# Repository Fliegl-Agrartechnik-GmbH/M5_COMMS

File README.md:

# M5_COMMS
M5_COMMS are CAN-Bus and Modbus Boards for M5 Stack

<https://github.com/espressif/esp-idf/issues/13989>

<https://community.m5stack.com/topic/306/plc-module/12?_=1718738548748>

4 Models: 
(right klick, open in new Tab for high-res view)

1. MAX3485, is a Fully 3.3V RS-485 Transceiver

2. LTC2877IMSE, is a 5V RS-485 Transceiver with a VIO Pin, so can interface to a 3.3V and even 1.8 V MCU

3. MAX485 is a 5V only Transceiver, using the Schottky Diode to not damage the ESP32 at RX.

4. CAN-Bus with a Infineon Transceiver

see: <https://github.com/Fliegl-Agrartechnik-GmbH/M5_COMMS/tree/main/CAN-BUS>

# lic
<p xmlns:cc="http://creativecommons.org/ns#" xmlns:dct="http://purl.org/dc/terms/"><a property="dct:title" rel="cc:attributionURL" href="https://github.com/Fliegl-Agrartechnik-GmbH/M5_COMMS">M5_COMMS</a> by <a rel="cc:attributionURL dct:creator" property="cc:attributionName" href="https://github.com/Fliegl-Agrartechnik-GmbH">Fliegl Agrartechnik GmbH</a> is licensed under <a href="https://creativecommons.org/licenses/by-sa/4.0/?ref=chooser-v1" target="_blank" rel="license noopener noreferrer" style="display:inline-block;">CC BY-SA 4.0</a></p>

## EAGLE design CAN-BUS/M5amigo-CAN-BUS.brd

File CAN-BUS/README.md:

# CAN-BUS

reffered also as TWAI

## Pinout

| **CAN**      | **RX** | **TX** |
|--------------|--------|--------|
| Core (Basic) | G36    | G25    |
| Core 2       | G36    | G25    |
| CoreS3       | G8     | G5     |

## External

| **Pin**  | **1**    | **2** | **3** | **4** |
|----------|----------|-------|-------|-------|
| Function | DC 9-24V | CAN_L | CAN_H | GND   |

## Testing

https://github.com/Fliegl-Agrartechnik-GmbH/twai_network

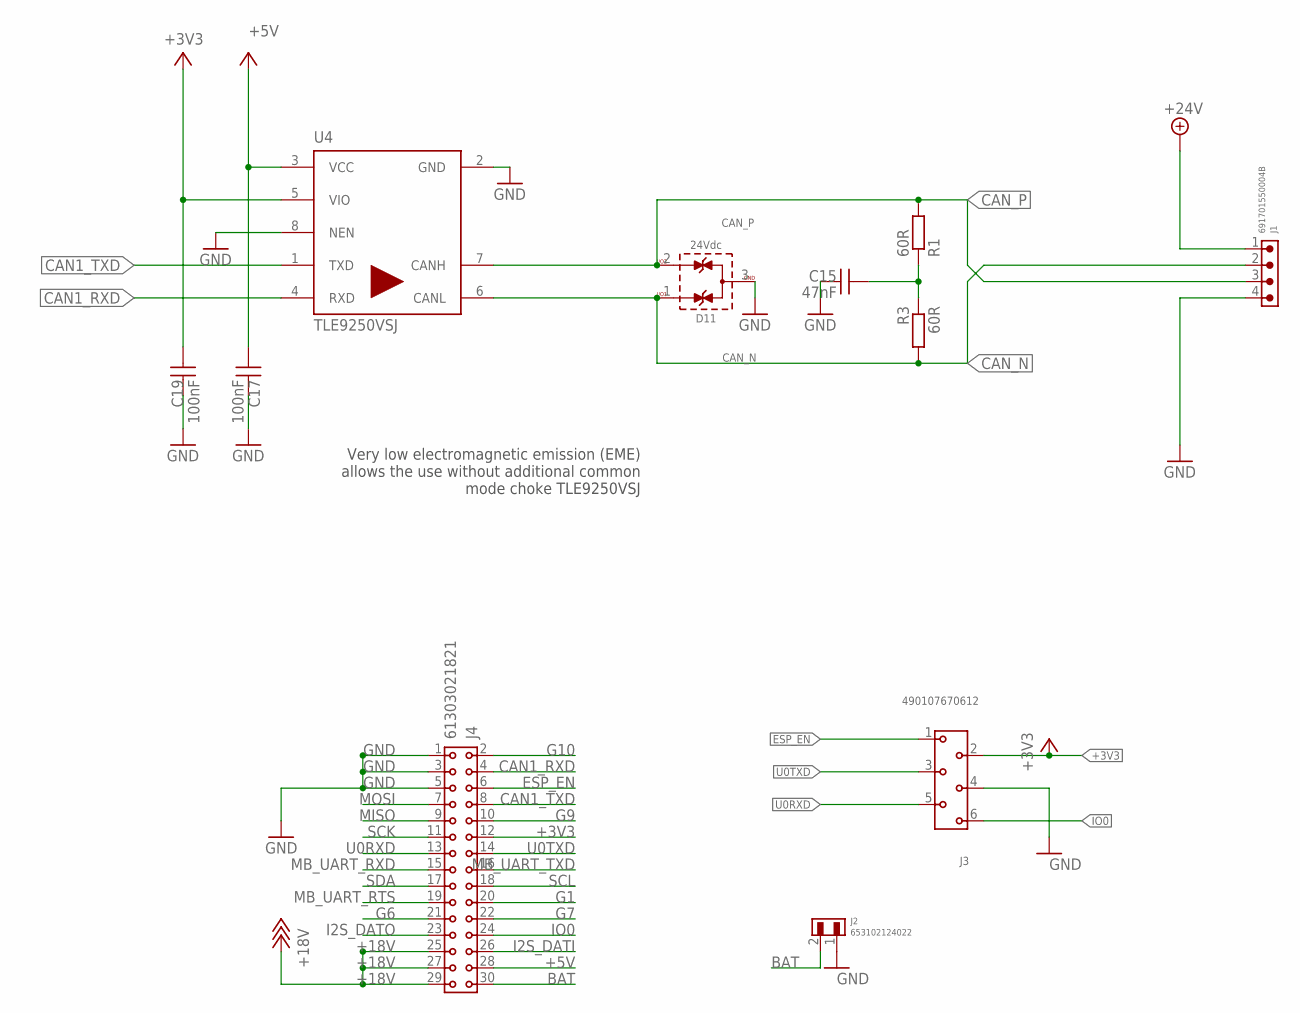
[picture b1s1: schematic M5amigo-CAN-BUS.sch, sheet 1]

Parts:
C15: 47nF; WCAP-CSGP_0805_H0.8_R
C17, C19: 100nF; WCAP-CSGP_0805_H0.8_R
D11: 24Vdc; WE-TVS_SOT23-3L
J1: 691701550004B
J2: 653102124022
J3: 490107670612; 490107670612_DEBUGGING
J4: 61303021821
R1, R3: 60R; R0805
U4: TLE9250VSJ; SOIC127P602X173-8N-V

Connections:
+3V3: C19.1, J3.2, J4.12, U4.5 (VIO)
+5V: C17.1, J4.28, U4.3 (VCC)
+18V: J4.25, J4.27, J4.29; also elsewhere on the board
+24V: J1.1; also elsewhere on the board
BAT: J2.2, J4.30
CAN1_RXD: J4.4, U4.4 (RXD)
CAN1_TXD: J4.8, U4.1 (TXD)
CAN_N: D11.1 (I/O1), J1.2, R3.2, U4.6 (CANL)
CAN_P: D11.2 (I/O2), J1.3, R1.2, U4.7 (CANH)
ESP_EN: J3.1, J4.6
G1: J4.20
G6: J4.21
G7: J4.22
G9: J4.10
G10: J4.2
GND: C15.2, C17.2, C19.2, D11.3 (GND), J1.4, J2.1, J3.4, J4.1, J4.3, J4.5, U4.2 (GND), U4.8 (NEN); also elsewhere on the board
I2S_DATI: J4.26
I2S_DATO: J4.23
IO0: J3.6, J4.24
MB_UART_RTS: J4.19
MB_UART_RXD: J4.15
MB_UART_TXD: J4.16
MISO: J4.9
MOSI: J4.7
unnamed: C15.1, R1.1, R3.1
SCK: J4.11
SCL: J4.18
SDA: J4.17
U0RXD: J3.5, J4.13
U0TXD: J3.3, J4.14

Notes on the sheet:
Very low electromagnetic emission (EME) allows the use without additional common mode choke TLE9250VSJ

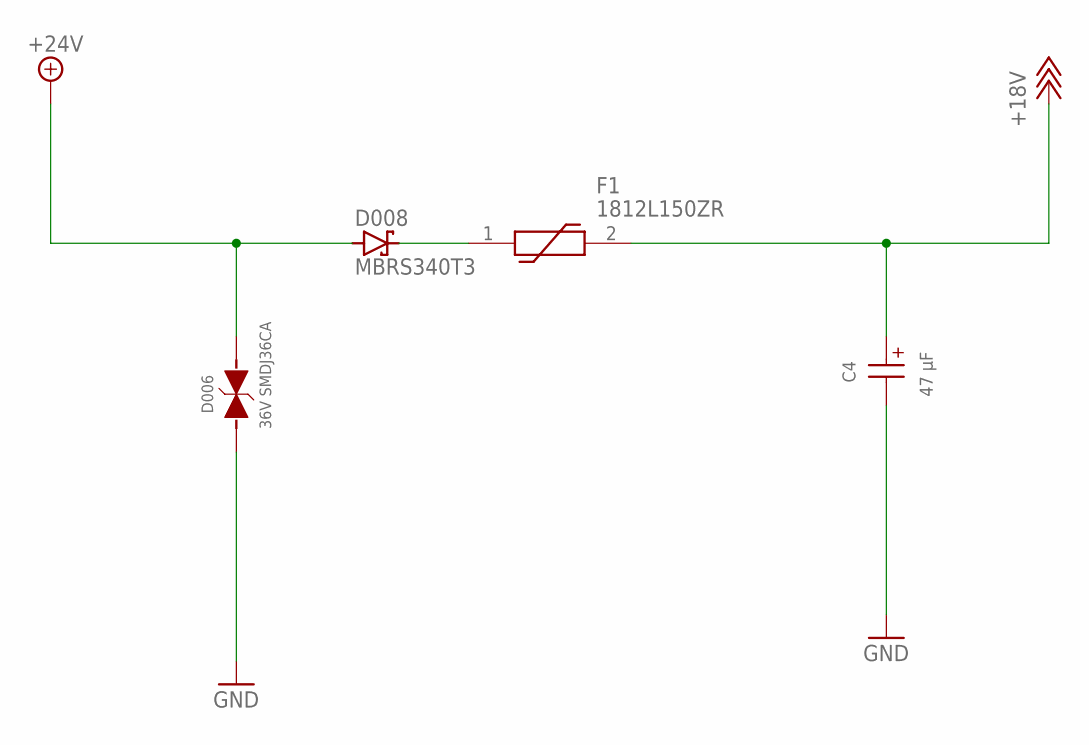
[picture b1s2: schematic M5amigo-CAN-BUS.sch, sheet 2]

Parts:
C4: 47 µF; WCAP-ASLL_6.3X7.7(DXL)
D006: 36V SMDJ36CA; WE-TVSP_DO-214AB_BIDIRECTIONAL
D008: MBRS340T3; SMC
F1: 1812L150ZR; 1812L010DR

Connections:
+18V: C4.1 (+), F1.2; also elsewhere on the board
+24V: D006.2, D008.A; also elsewhere on the board
GND: C4.2 (-), D006.1; also elsewhere on the board
unnamed: D008.C, F1.1

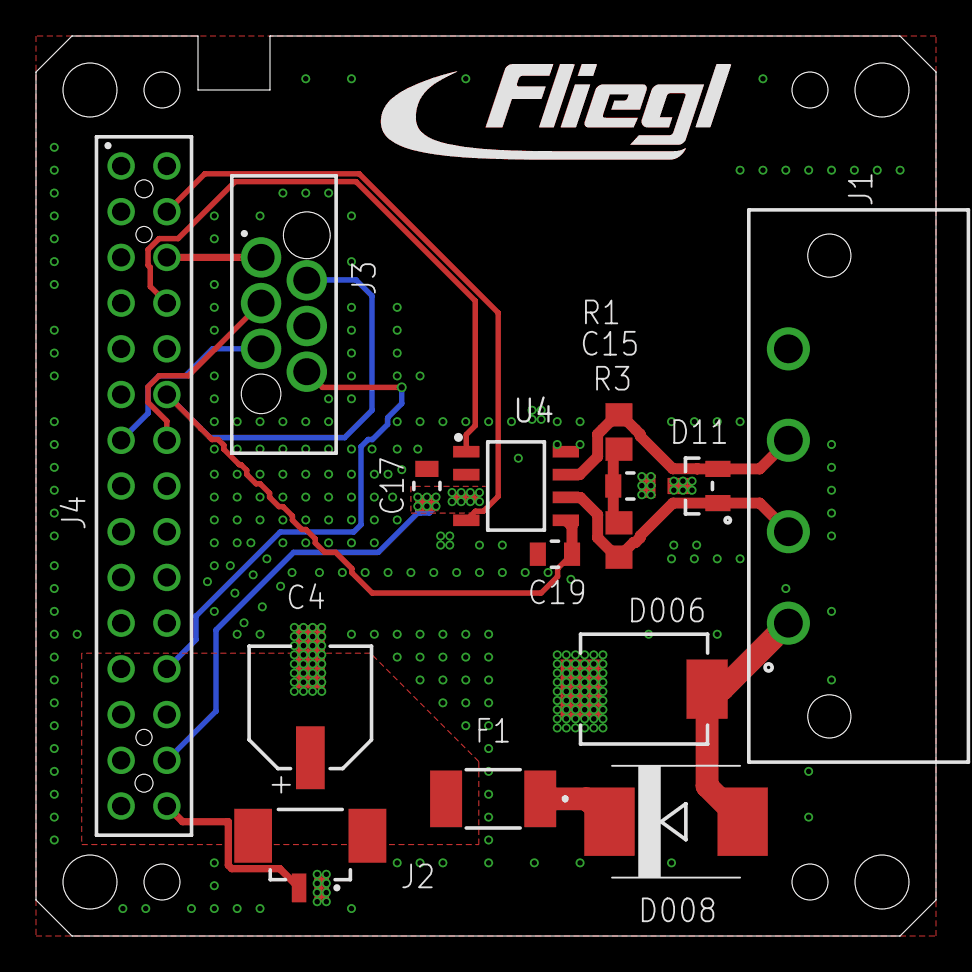
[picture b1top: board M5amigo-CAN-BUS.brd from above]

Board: 2 copper layers, 50.0 x 50.0 mm, 16 parts (0 on the bottom side), 16 nets.

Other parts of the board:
U$2: FLIEGL_LOGO_19.5X5.3MM_TOP+TPLACE

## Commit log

2024-07-25 Update LICENSE
2024-07-25 Add gitignore rules for temporary files and add new PCB layout file with layer definitions.
2024-08-16 Add README with CAN-BUS pinout and testing link
    A new README file was added with information on CAN-BUS pinout for different cores and external connections. It also includes a link for testing details.

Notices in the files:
parts and their libraries:
Wurth_Connectors_WR-PHD: Copyright: Würth Elektronik
